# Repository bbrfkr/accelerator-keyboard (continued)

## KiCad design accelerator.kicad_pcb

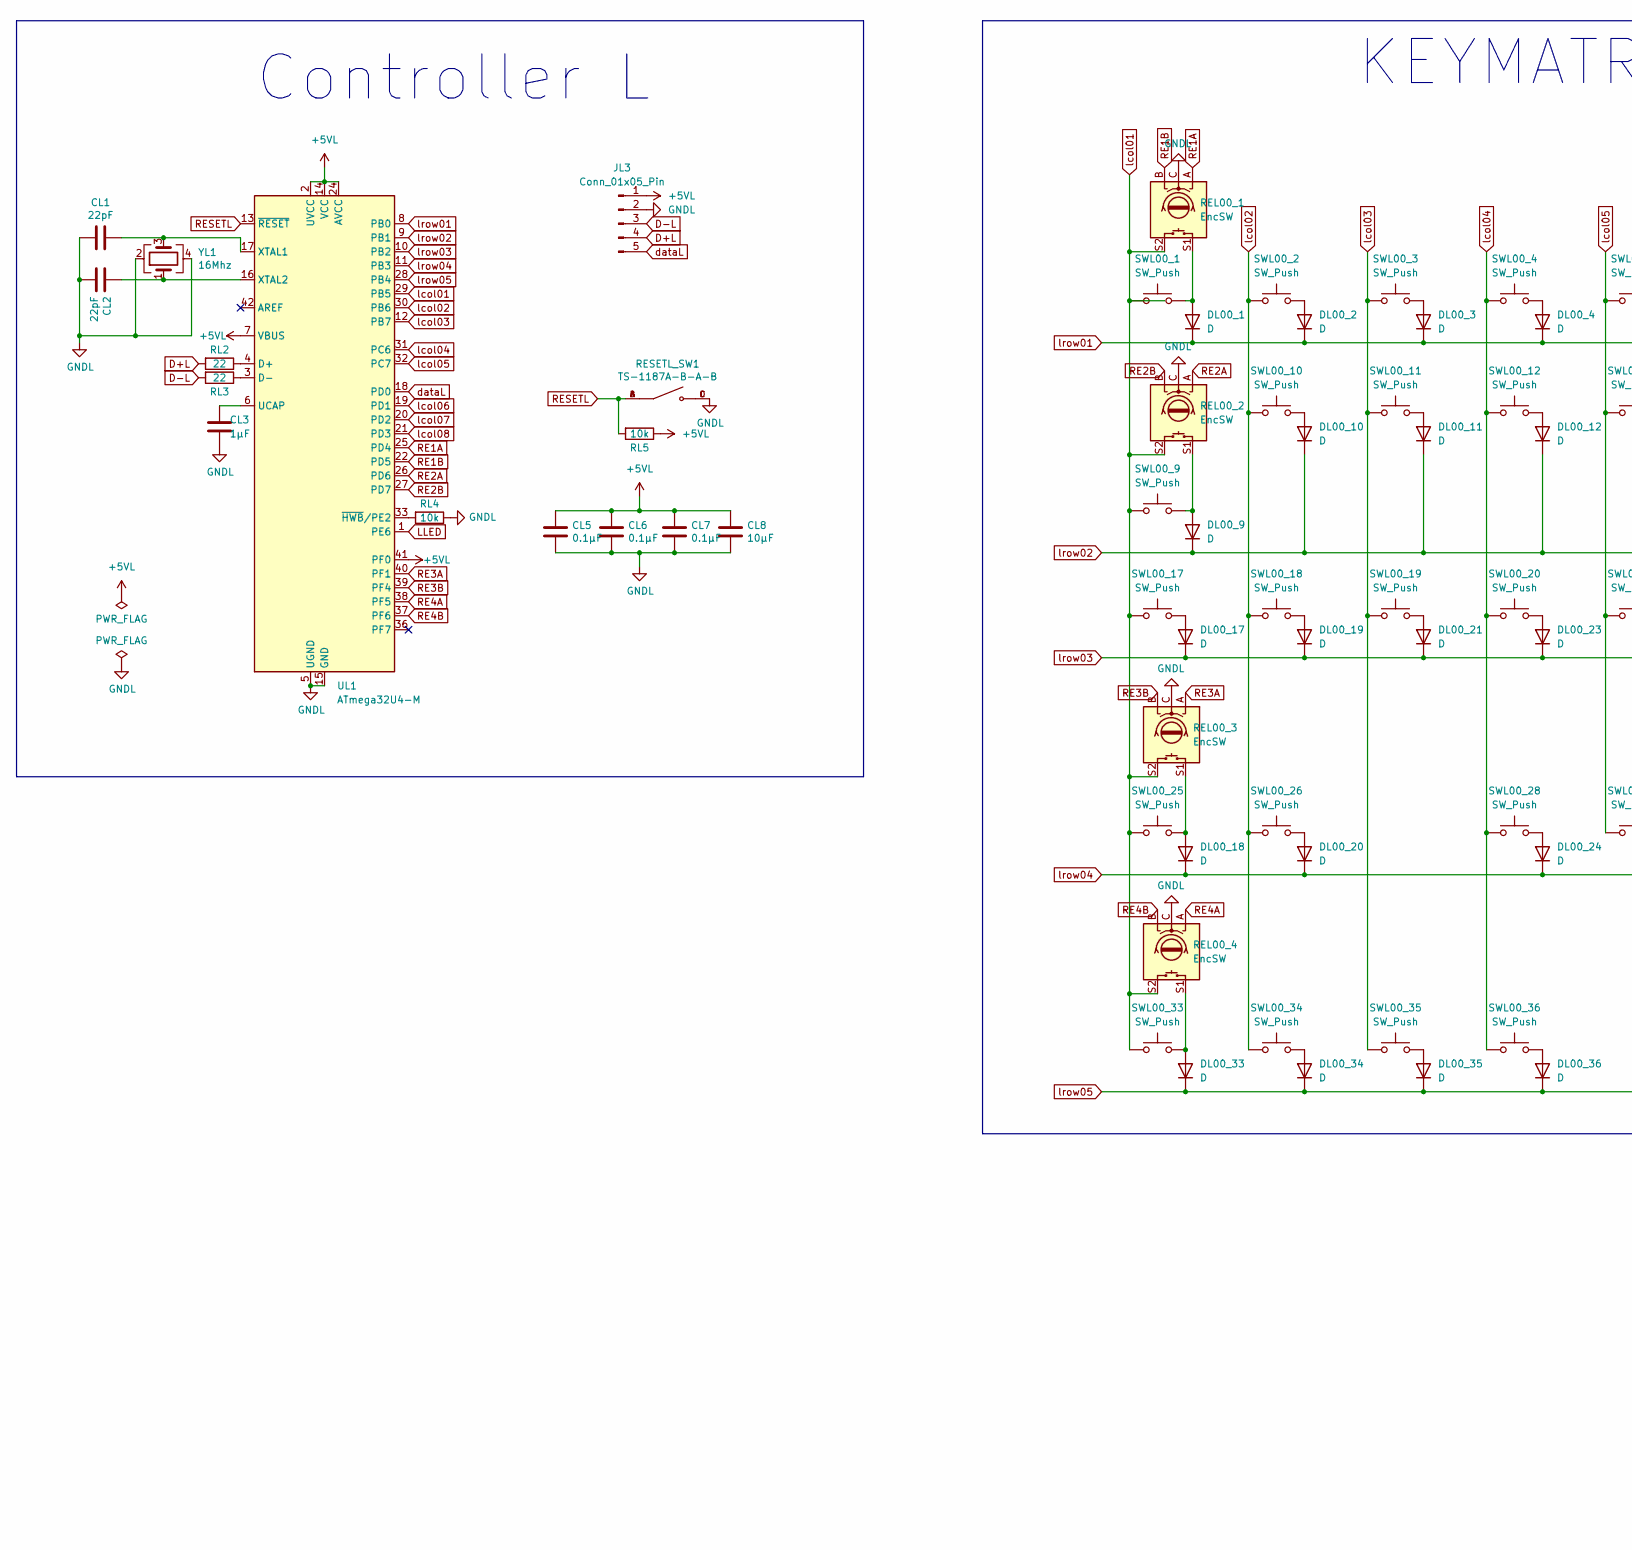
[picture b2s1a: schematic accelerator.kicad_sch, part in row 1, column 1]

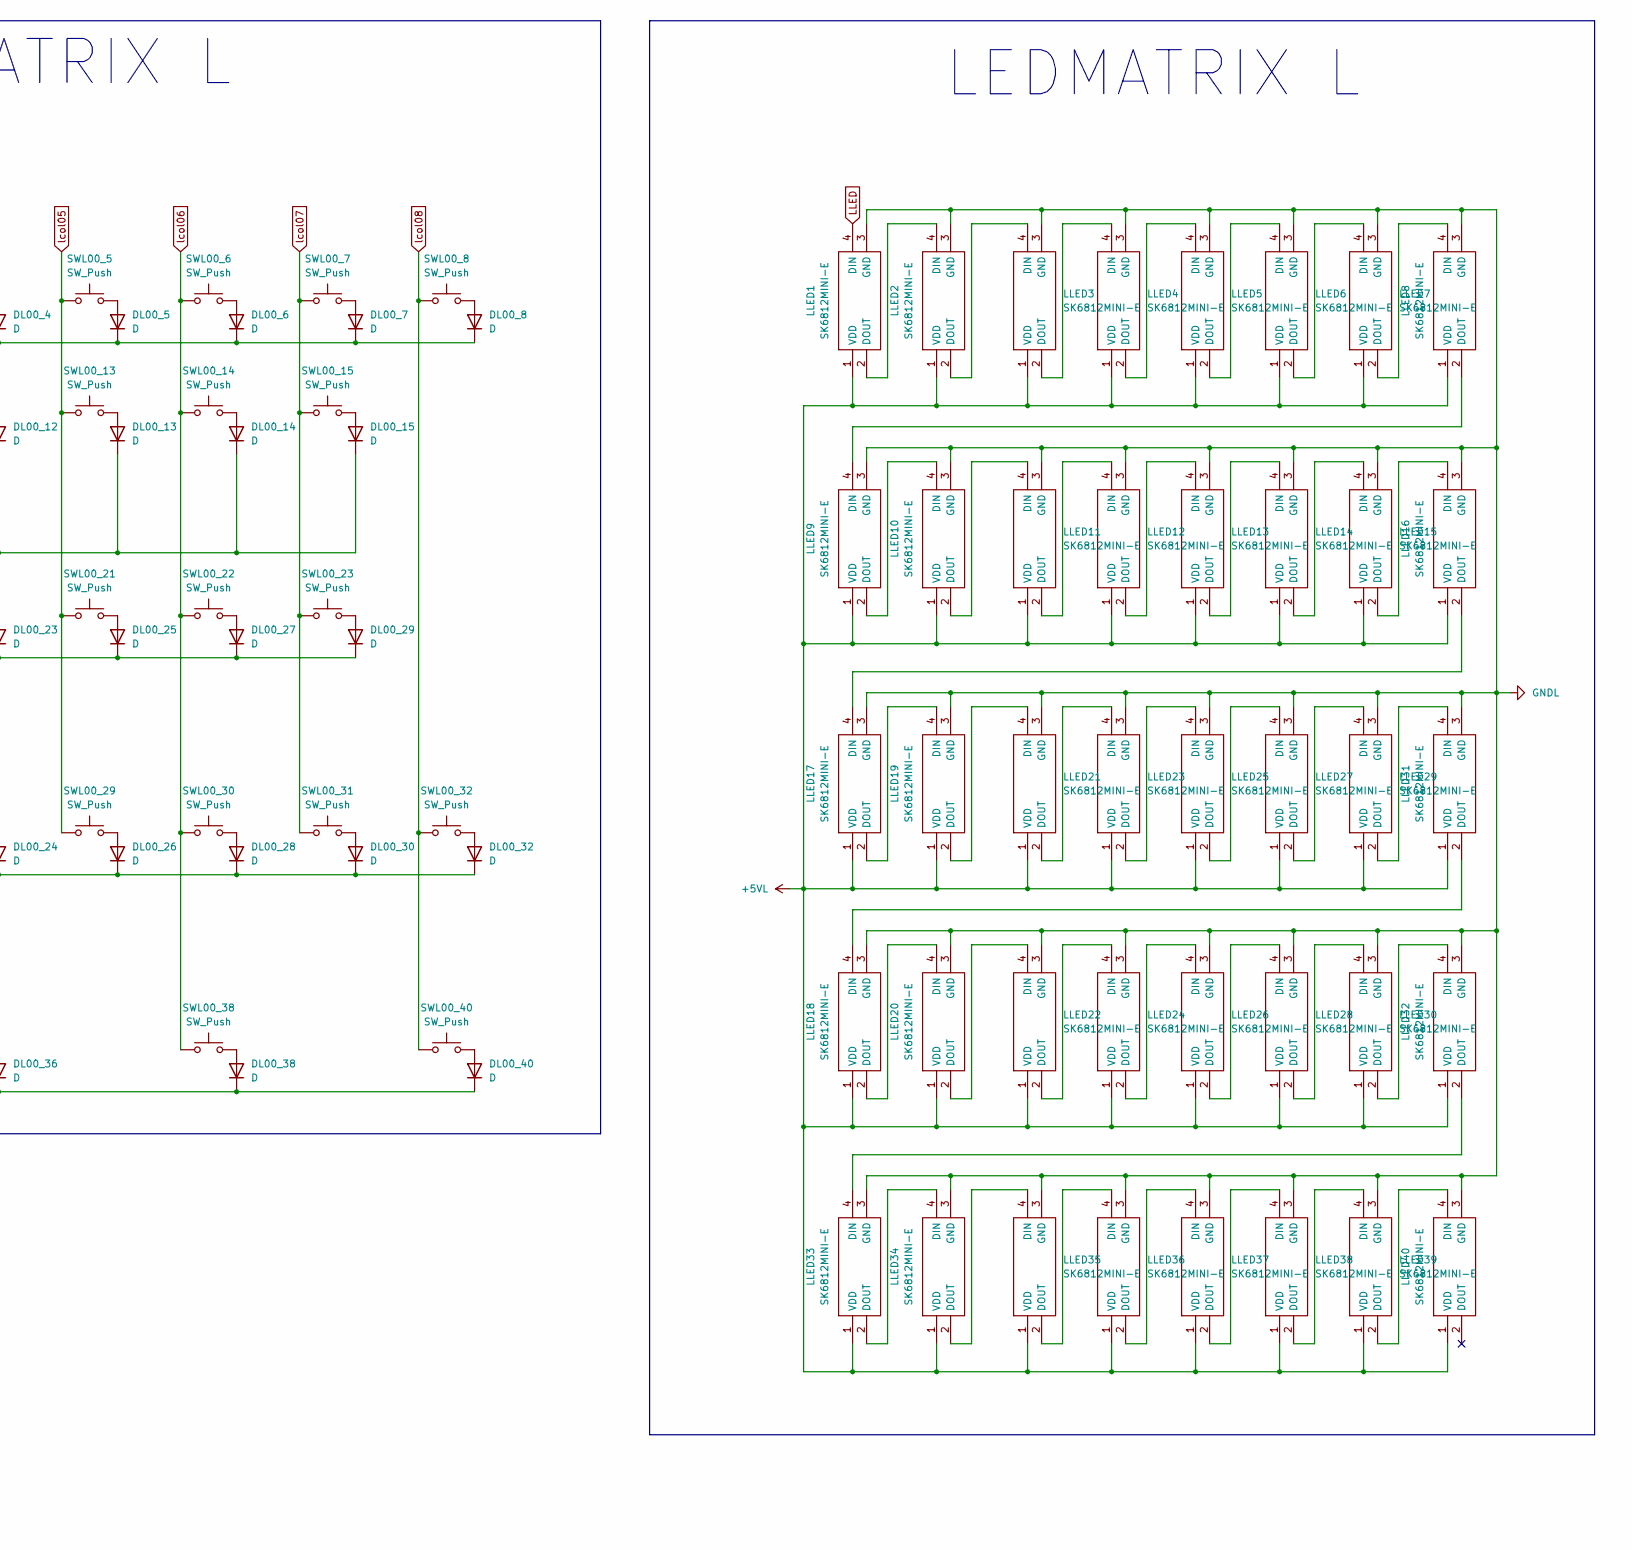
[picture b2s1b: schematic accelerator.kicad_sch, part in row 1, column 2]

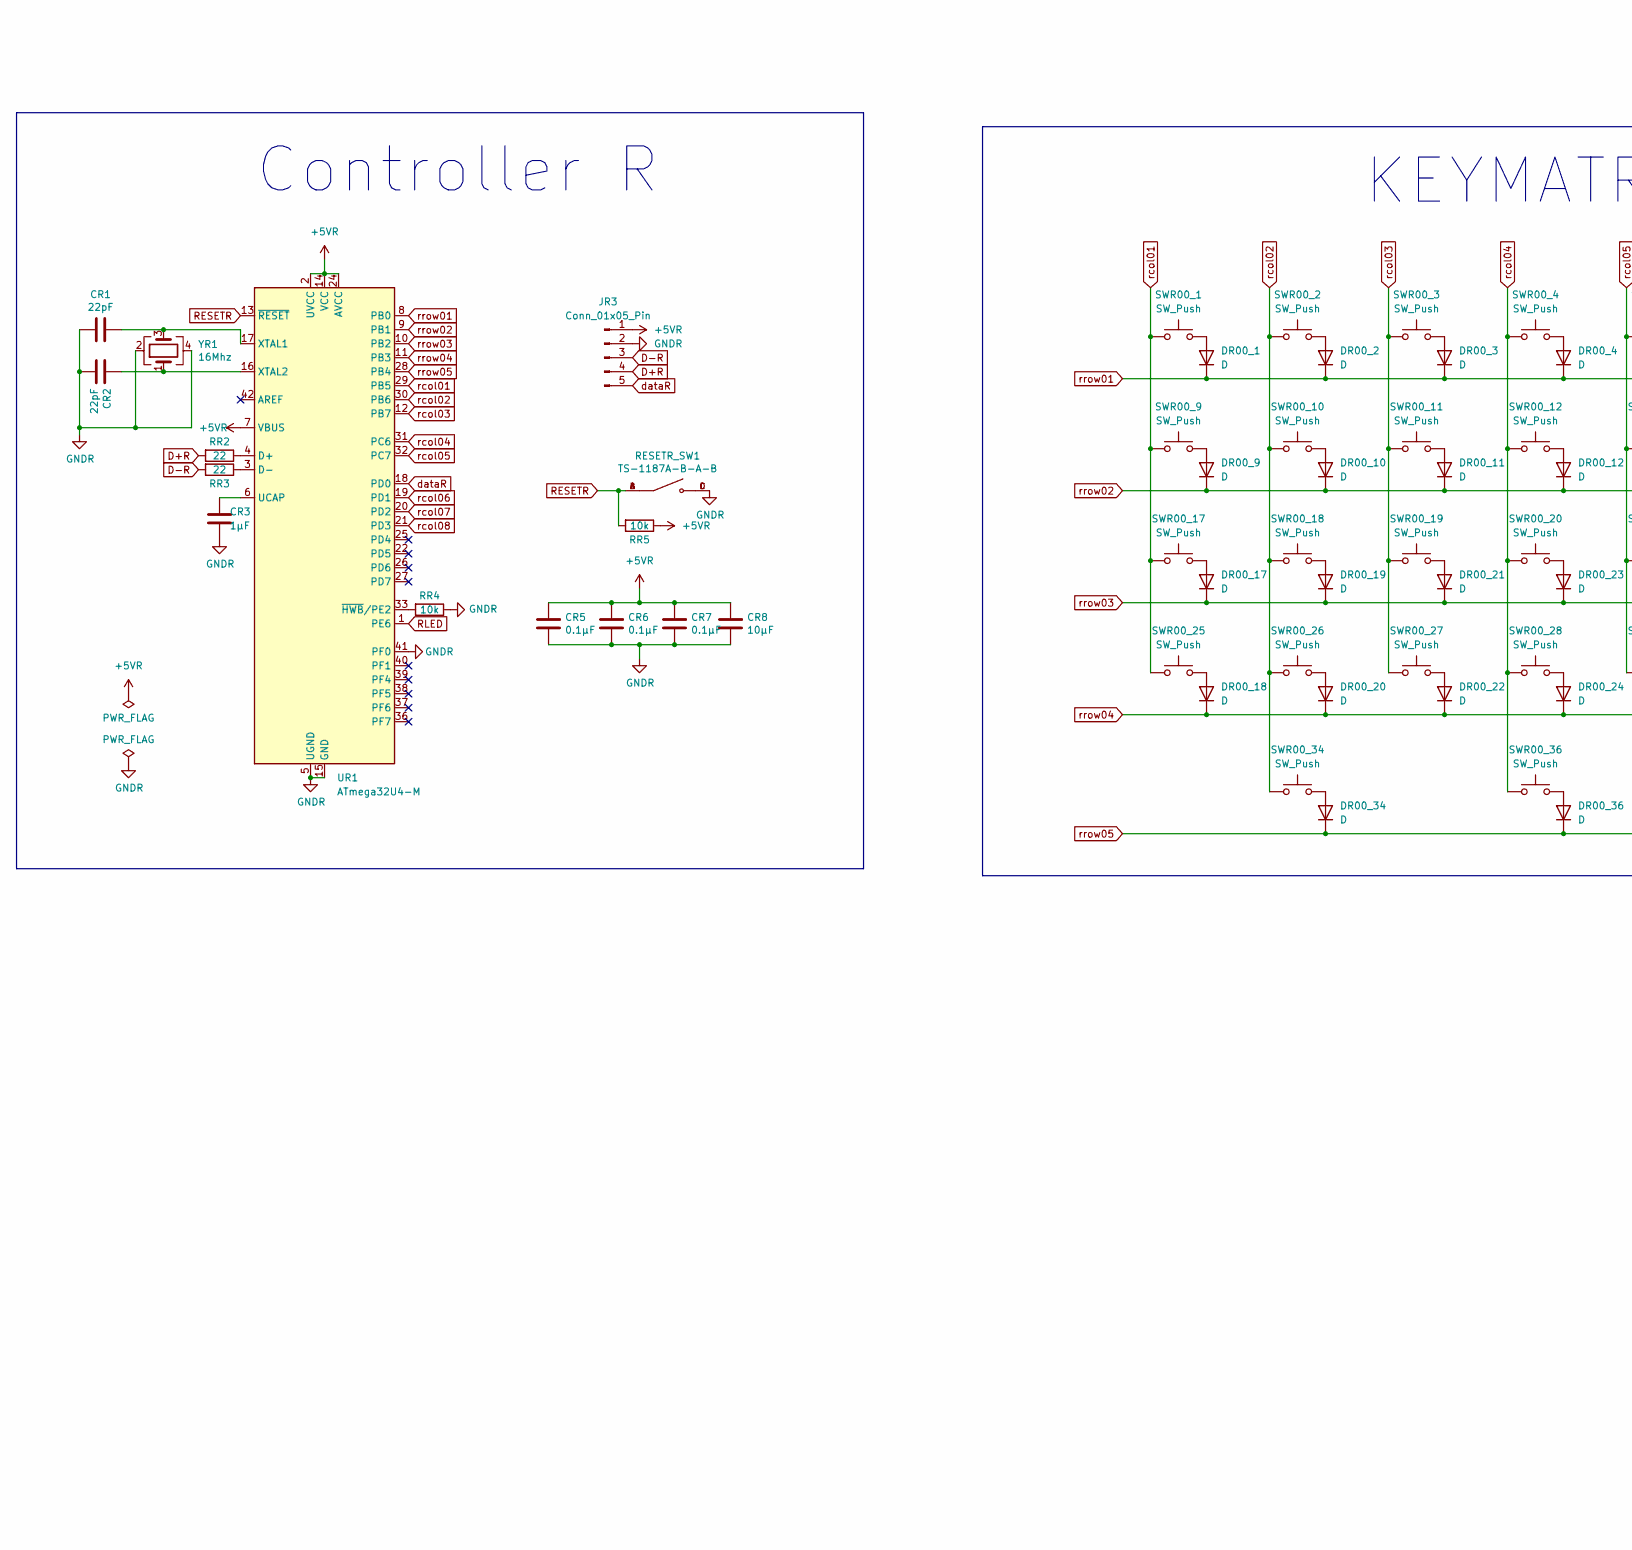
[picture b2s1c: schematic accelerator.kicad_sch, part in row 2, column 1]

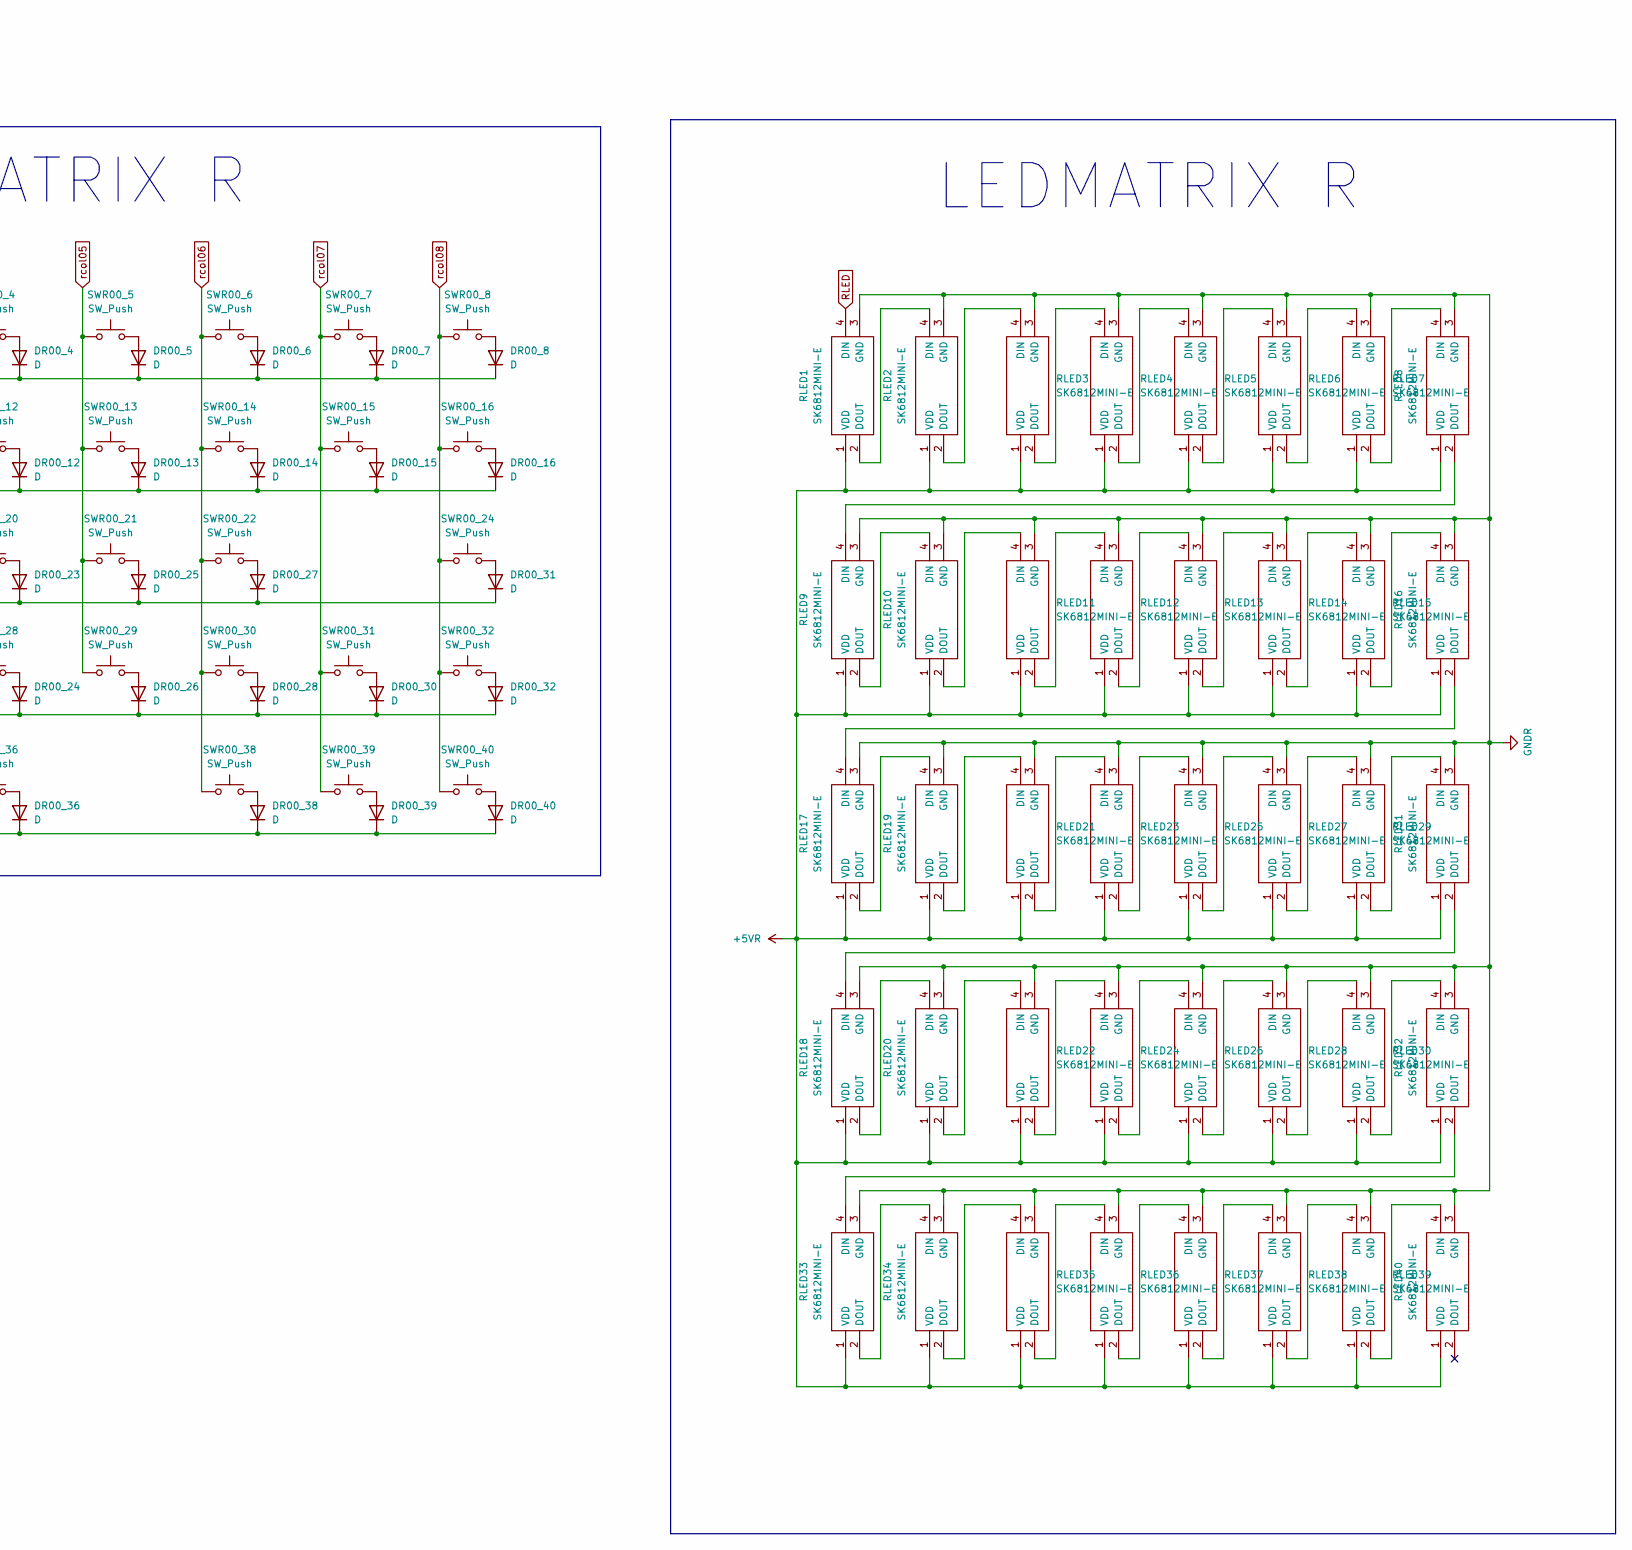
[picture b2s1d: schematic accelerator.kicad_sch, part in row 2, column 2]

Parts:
CL1, CL2: 22pF; C_1206_3216Metric; LCSC C107174
CL3: 1μF; C_1206_3216Metric; LCSC C1848
CL5, CL6, CL7: 0.1μF; C_1206_3216Metric; LCSC C24497
CL8: 10μF; C_1206_3216Metric; LCSC C13585
CR1, CR2: 22pF; C_1206_3216Metric; LCSC C107174
CR3: 1μF; C_1206_3216Metric; LCSC C1848
CR5, CR6, CR7: 0.1μF; C_1206_3216Metric; LCSC C24497
CR8: 10μF; C_1206_3216Metric; LCSC C13585
DL00_1, DL00_2, DL00_3, DL00_4, DL00_5, DL00_6, DL00_7, DL00_8, DL00_9, DL00_10, DL00_11, DL00_12, DL00_13, DL00_14, DL00_15, DL00_17, DL00_18, DL00_19, DL00_20, DL00_21, DL00_23, DL00_24, DL00_25, DL00_26, DL00_27, DL00_28, DL00_29, DL00_30, DL00_32, DL00_33, DL00_34, DL00_35, DL00_36, DL00_38, DL00_40: D; D_SOD-123-Pretty; LCSC C81598
DR00_1, DR00_2, DR00_3, DR00_4, DR00_5, DR00_6, DR00_7, DR00_8, DR00_9, DR00_10, DR00_11, DR00_12, DR00_13, DR00_14, DR00_15, DR00_16, DR00_17, DR00_18, DR00_19, DR00_20, DR00_21, DR00_22, DR00_23, DR00_24, DR00_25, DR00_26, DR00_27, DR00_28, DR00_30, DR00_31, DR00_32, DR00_34, DR00_36, DR00_38, DR00_39, DR00_40: D; D_SOD-123-Pretty; LCSC C81598
JL3: Conn_01x05_Pin; JST_PH_S5B-PH-K_1x05_P2.00mm_Horizontal
JR3: Conn_01x05_Pin; JST_PH_S5B-PH-K_1x05_P2.00mm_Horizontal
LLED1, LLED2, LLED3, LLED4, LLED5, LLED6, LLED7, LLED8, LLED9, LLED10, LLED11, LLED12, LLED13, LLED14, LLED15, LLED16, LLED17, LLED18, LLED19, LLED20, LLED21, LLED22, LLED23, LLED24, LLED25, LLED26, LLED27, LLED28, LLED29, LLED30, LLED31, LLED32, LLED33, LLED34, LLED35, LLED36, LLED37, LLED38, LLED39, LLED40: SK6812MINI-E; SK6812MINIE; Manufacturer_Part_Number SK6812MINI-E; LCSC C5149201
REL00_1, REL00_2, REL00_3, REL00_4: EncSW; RotaryEncoder_Alps_EC12E-Switch_Vertical_H20mm
RESETL_SW1: TS-1187A-B-A-B; SW_TS-1187A-B-A-B; PARTREV A0; LCSC C318884
RESETR_SW1: TS-1187A-B-A-B; SW_TS-1187A-B-A-B; PARTREV A0; LCSC C318884
RL2, RL3: 22; R_1206_3216Metric; LCSC C17958
RL4, RL5: 10k; R_1206_3216Metric; LCSC C17928
RLED1, RLED2, RLED3, RLED4, RLED5, RLED6, RLED7, RLED8, RLED9, RLED10, RLED11, RLED12, RLED13, RLED14, RLED15, RLED16, RLED17, RLED18, RLED19, RLED20, RLED21, RLED22, RLED23, RLED24, RLED25, RLED26, RLED27, RLED28, RLED29, RLED30, RLED31, RLED32, RLED33, RLED34, RLED35, RLED36, RLED37, RLED38, RLED39, RLED40: SK6812MINI-E; SK6812MINIE; Manufacturer_Part_Number SK6812MINI-E; LCSC C5149201
RR2, RR3: 22; R_1206_3216Metric; LCSC C17958
RR4, RR5: 10k; R_1206_3216Metric; LCSC C17928
SWL00_1, SWL00_2, SWL00_3, SWL00_4, SWL00_5, SWL00_6, SWL00_7, SWL00_8, SWL00_9, SWL00_11, SWL00_12, SWL00_13, SWL00_14, SWL00_15, SWL00_17, SWL00_19, SWL00_20, SWL00_21, SWL00_22, SWL00_23, SWL00_25, SWL00_28, SWL00_29, SWL00_30, SWL00_31, SWL00_32, SWL00_33: SW_Push; MXOnly-1U-Hotswap; LCSC C5156480
SWL00_10: SW_Push; MXOnly-1.5U-Hotswap; LCSC C5156480
SWL00_18: SW_Push; MXOnly-1.75U-Hotswap; LCSC C5156480
SWL00_26: SW_Push; MXOnly-2.25U-Hotswap; LCSC C5156480
SWL00_34, SWL00_35, SWL00_36, SWL00_40: SW_Push; MXOnly-1.25U-Hotswap; LCSC C5156480
SWL00_38: SW_Push; MXOnly-2.25U-Hotswap-ReversedStabilizers; LCSC C5156480
SWR00_1, SWR00_2, SWR00_3, SWR00_4, SWR00_5, SWR00_6, SWR00_7, SWR00_9, SWR00_10, SWR00_11, SWR00_12, SWR00_13, SWR00_14, SWR00_15, SWR00_17, SWR00_18, SWR00_19, SWR00_20, SWR00_21, SWR00_22, SWR00_25, SWR00_26, SWR00_27, SWR00_28, SWR00_29, SWR00_30, SWR00_32: SW_Push; MXOnly-1U-Hotswap; LCSC C5156480
SWR00_8: SW_Push; MXOnly-2U-Hotswap; LCSC C5156480
SWR00_16: SW_Push; MXOnly-1.5U-Hotswap; LCSC C5156480
SWR00_24: SW_Push; MXOnly-2.25U-Hotswap; LCSC C5156480
SWR00_31: SW_Push; MXOnly-1.75U-Hotswap; LCSC C5156480
SWR00_34: SW_Push; MXOnly-2.75U-Hotswap-ReversedStabilizers; LCSC C5156480
SWR00_36: SW_Push; MXOnly-2.25U-Hotswap-ReversedStabilizers; LCSC C5156480
SWR00_38, SWR00_39, SWR00_40: SW_Push; MXOnly-1.25U-Hotswap; LCSC C5156480
UL1: ATmega32U4-M; QFN-44-1EP_7x7mm_P0.5mm_EP5.2x5.2mm; LCSC C112161
UR1: ATmega32U4-M; QFN-44-1EP_7x7mm_P0.5mm_EP5.2x5.2mm; LCSC C112161
YL1: 16Mhz; OSC-SMD_4P-L3.2-W2.5-BL; LCSC C13738
YR1: 16Mhz; OSC-SMD_4P-L3.2-W2.5-BL; LCSC C13738

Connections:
+5VL: CL5.1, CL6.1, CL7.1, CL8.1, JL3.1, LLED1.1 (VDD), LLED2.1 (VDD), LLED3.1 (VDD), LLED4.1 (VDD), LLED5.1 (VDD), LLED6.1 (VDD), LLED7.1 (VDD), LLED8.1 (VDD), LLED9.1 (VDD), LLED10.1 (VDD), LLED11.1 (VDD), LLED12.1 (VDD), LLED13.1 (VDD), LLED14.1 (VDD), LLED15.1 (VDD), LLED16.1 (VDD), LLED17.1 (VDD), LLED18.1 (VDD), LLED19.1 (VDD), LLED20.1 (VDD), LLED21.1 (VDD), LLED22.1 (VDD), LLED23.1 (VDD), LLED24.1 (VDD), LLED25.1 (VDD), LLED26.1 (VDD), LLED27.1 (VDD), LLED28.1 (VDD), LLED29.1 (VDD), LLED30.1 (VDD), LLED31.1 (VDD), LLED32.1 (VDD), LLED33.1 (VDD), LLED34.1 (VDD), LLED35.1 (VDD), LLED36.1 (VDD), LLED37.1 (VDD), LLED38.1 (VDD), LLED39.1 (VDD), LLED40.1 (VDD), RL5.1, UL1.2 (UVCC), UL1.7 (VBUS), UL1.14 (VCC), UL1.24 (AVCC), UL1.34 (VCC), UL1.41 (PF0), UL1.44 (AVCC)
+5VR: CR5.1, CR6.1, CR7.1, CR8.1, JR3.1, RLED1.1 (VDD), RLED2.1 (VDD), RLED3.1 (VDD), RLED4.1 (VDD), RLED5.1 (VDD), RLED6.1 (VDD), RLED7.1 (VDD), RLED8.1 (VDD), RLED9.1 (VDD), RLED10.1 (VDD), RLED11.1 (VDD), RLED12.1 (VDD), RLED13.1 (VDD), RLED14.1 (VDD), RLED15.1 (VDD), RLED16.1 (VDD), RLED17.1 (VDD), RLED18.1 (VDD), RLED19.1 (VDD), RLED20.1 (VDD), RLED21.1 (VDD), RLED22.1 (VDD), RLED23.1 (VDD), RLED24.1 (VDD), RLED25.1 (VDD), RLED26.1 (VDD), RLED27.1 (VDD), RLED28.1 (VDD), RLED29.1 (VDD), RLED30.1 (VDD), RLED31.1 (VDD), RLED32.1 (VDD), RLED33.1 (VDD), RLED34.1 (VDD), RLED35.1 (VDD), RLED36.1 (VDD), RLED37.1 (VDD), RLED38.1 (VDD), RLED39.1 (VDD), RLED40.1 (VDD), RR5.1, UR1.2 (UVCC), UR1.7 (VBUS), UR1.14 (VCC), UR1.24 (AVCC), UR1.34 (VCC), UR1.44 (AVCC)
D+L: JL3.4, RL2.2
D+R: JR3.4, RR2.2
D-L: JL3.3, RL3.2
D-R: JR3.3, RR3.2
GNDL: CL1.1, CL2.2, CL3.2, CL5.2, CL6.2, CL7.2, CL8.2, JL3.2, LLED1.3 (GND), LLED2.3 (GND), LLED3.3 (GND), LLED4.3 (GND), LLED5.3 (GND), LLED6.3 (GND), LLED7.3 (GND), LLED8.3 (GND), LLED9.3 (GND), LLED10.3 (GND), LLED11.3 (GND), LLED12.3 (GND), LLED13.3 (GND), LLED14.3 (GND), LLED15.3 (GND), LLED16.3 (GND), LLED17.3 (GND), LLED18.3 (GND), LLED19.3 (GND), LLED20.3 (GND), LLED21.3 (GND), LLED22.3 (GND), LLED23.3 (GND), LLED24.3 (GND), LLED25.3 (GND), LLED26.3 (GND), LLED27.3 (GND), LLED28.3 (GND), LLED29.3 (GND), LLED30.3 (GND), LLED31.3 (GND), LLED32.3 (GND), LLED33.3 (GND), LLED34.3 (GND), LLED35.3 (GND), LLED36.3 (GND), LLED37.3 (GND), LLED38.3 (GND), LLED39.3 (GND), LLED40.3 (GND), REL00_1.C, REL00_2.C, REL00_3.C, REL00_4.C, RESETL_SW1.C, RESETL_SW1.D, RL4.1, UL1.5 (UGND), UL1.15 (GND), UL1.23 (GND), UL1.35 (GND), UL1.43 (GND), UL1.45 (GND), YL1.2, YL1.4
GNDR: CR1.1, CR2.2, CR3.2, CR5.2, CR6.2, CR7.2, CR8.2, JR3.2, RESETR_SW1.C, RESETR_SW1.D, RLED1.3 (GND), RLED2.3 (GND), RLED3.3 (GND), RLED4.3 (GND), RLED5.3 (GND), RLED6.3 (GND), RLED7.3 (GND), RLED8.3 (GND), RLED9.3 (GND), RLED10.3 (GND), RLED11.3 (GND), RLED12.3 (GND), RLED13.3 (GND), RLED14.3 (GND), RLED15.3 (GND), RLED16.3 (GND), RLED17.3 (GND), RLED18.3 (GND), RLED19.3 (GND), RLED20.3 (GND), RLED21.3 (GND), RLED22.3 (GND), RLED23.3 (GND), RLED24.3 (GND), RLED25.3 (GND), RLED26.3 (GND), RLED27.3 (GND), RLED28.3 (GND), RLED29.3 (GND), RLED30.3 (GND), RLED31.3 (GND), RLED32.3 (GND), RLED33.3 (GND), RLED34.3 (GND), RLED35.3 (GND), RLED36.3 (GND), RLED37.3 (GND), RLED38.3 (GND), RLED39.3 (GND), RLED40.3 (GND), RR4.1, UR1.5 (UGND), UR1.15 (GND), UR1.23 (GND), UR1.35 (GND), UR1.41 (PF0), UR1.43 (GND), UR1.45 (GND), YR1.2, YR1.4
LLED: LLED1.4 (DIN), UL1.1 (PE6)
unnamed: DL00_1.2 (A), REL00_1.S1, SWL00_1.2
unnamed: DL00_2.2 (A), SWL00_2.2
unnamed: DL00_3.2 (A), SWL00_3.2
unnamed: DL00_4.2 (A), SWL00_4.2
unnamed: DL00_5.2 (A), SWL00_5.2
unnamed: DL00_6.2 (A), SWL00_6.2
unnamed: DL00_7.2 (A), SWL00_7.2
unnamed: DL00_8.2 (A), SWL00_8.2
unnamed: DL00_9.2 (A), REL00_2.S1, SWL00_9.2
unnamed: DL00_10.2 (A), SWL00_10.2
unnamed: DL00_11.2 (A), SWL00_11.2
unnamed: DL00_12.2 (A), SWL00_12.2
unnamed: DL00_13.2 (A), SWL00_13.2
unnamed: DL00_14.2 (A), SWL00_14.2
unnamed: DL00_15.2 (A), SWL00_15.2
unnamed: DL00_17.2 (A), SWL00_17.2
unnamed: DL00_18.2 (A), REL00_3.S1, SWL00_25.2
unnamed: DL00_19.2 (A), SWL00_18.2
unnamed: DL00_20.2 (A), SWL00_26.2
unnamed: DL00_21.2 (A), SWL00_19.2
unnamed: DL00_23.2 (A), SWL00_20.2
unnamed: DL00_24.2 (A), SWL00_28.2
unnamed: DL00_25.2 (A), SWL00_21.2
unnamed: DL00_26.2 (A), SWL00_29.2
unnamed: DL00_27.2 (A), SWL00_22.2
unnamed: DL00_28.2 (A), SWL00_30.2
unnamed: DL00_29.2 (A), SWL00_23.2
unnamed: DL00_30.2 (A), SWL00_31.2
unnamed: DL00_32.2 (A), SWL00_32.2
unnamed: DL00_33.2 (A), REL00_4.S1, SWL00_33.2
unnamed: DL00_34.2 (A), SWL00_34.2
unnamed: DL00_35.2 (A), SWL00_35.2
unnamed: DL00_36.2 (A), SWL00_36.2
unnamed: DL00_38.2 (A), SWL00_38.2
unnamed: DL00_40.2 (A), SWL00_40.2
unnamed: DR00_1.2 (A), SWR00_1.2
unnamed: DR00_2.2 (A), SWR00_2.2
unnamed: DR00_3.2 (A), SWR00_3.2
unnamed: DR00_4.2 (A), SWR00_4.2
unnamed: DR00_5.2 (A), SWR00_5.2
unnamed: DR00_6.2 (A), SWR00_6.2
unnamed: DR00_7.2 (A), SWR00_7.2
unnamed: DR00_8.2 (A), SWR00_8.2
unnamed: DR00_9.2 (A), SWR00_9.2
unnamed: DR00_10.2 (A), SWR00_10.2
unnamed: DR00_11.2 (A), SWR00_11.2
unnamed: DR00_12.2 (A), SWR00_12.2
unnamed: DR00_13.2 (A), SWR00_13.2
unnamed: DR00_14.2 (A), SWR00_14.2
unnamed: DR00_15.2 (A), SWR00_15.2
unnamed: DR00_16.2 (A), SWR00_16.2
unnamed: DR00_17.2 (A), SWR00_17.2
unnamed: DR00_18.2 (A), SWR00_25.2
unnamed: DR00_19.2 (A), SWR00_18.2
unnamed: DR00_20.2 (A), SWR00_26.2
unnamed: DR00_21.2 (A), SWR00_19.2
unnamed: DR00_22.2 (A), SWR00_27.2
unnamed: DR00_23.2 (A), SWR00_20.2
unnamed: DR00_24.2 (A), SWR00_28.2
unnamed: DR00_25.2 (A), SWR00_21.2
unnamed: DR00_26.2 (A), SWR00_29.2
unnamed: DR00_27.2 (A), SWR00_22.2
unnamed: DR00_28.2 (A), SWR00_30.2
unnamed: DR00_30.2 (A), SWR00_31.2
unnamed: DR00_31.2 (A), SWR00_24.2
unnamed: DR00_32.2 (A), SWR00_32.2
unnamed: DR00_34.2 (A), SWR00_34.2
unnamed: DR00_36.2 (A), SWR00_36.2
unnamed: DR00_38.2 (A), SWR00_38.2
unnamed: DR00_39.2 (A), SWR00_39.2
unnamed: DR00_40.2 (A), SWR00_40.2
unnamed: LLED1.2 (DOUT), LLED2.4 (DIN)
unnamed: LLED2.2 (DOUT), LLED3.4 (DIN)
unnamed: LLED3.2 (DOUT), LLED4.4 (DIN)
unnamed: LLED4.2 (DOUT), LLED5.4 (DIN)
unnamed: LLED5.2 (DOUT), LLED6.4 (DIN)
unnamed: LLED6.2 (DOUT), LLED7.4 (DIN)
unnamed: LLED7.2 (DOUT), LLED8.4 (DIN)
unnamed: LLED8.2 (DOUT), LLED9.4 (DIN)
unnamed: LLED9.2 (DOUT), LLED10.4 (DIN)
unnamed: LLED10.2 (DOUT), LLED11.4 (DIN)
unnamed: LLED11.2 (DOUT), LLED12.4 (DIN)
unnamed: LLED12.2 (DOUT), LLED13.4 (DIN)
unnamed: LLED13.2 (DOUT), LLED14.4 (DIN)
unnamed: LLED14.2 (DOUT), LLED15.4 (DIN)
unnamed: LLED15.2 (DOUT), LLED16.4 (DIN)
unnamed: LLED16.2 (DOUT), LLED17.4 (DIN)
unnamed: LLED17.2 (DOUT), LLED19.4 (DIN)
unnamed: LLED18.4 (DIN), LLED31.2 (DOUT)
unnamed: LLED18.2 (DOUT), LLED20.4 (DIN)
unnamed: LLED19.2 (DOUT), LLED21.4 (DIN)
unnamed: LLED20.2 (DOUT), LLED22.4 (DIN)
unnamed: LLED21.2 (DOUT), LLED23.4 (DIN)
unnamed: LLED22.2 (DOUT), LLED24.4 (DIN)
unnamed: LLED23.2 (DOUT), LLED25.4 (DIN)
unnamed: LLED24.2 (DOUT), LLED26.4 (DIN)
unnamed: LLED25.2 (DOUT), LLED27.4 (DIN)
unnamed: LLED26.2 (DOUT), LLED28.4 (DIN)
unnamed: LLED27.2 (DOUT), LLED29.4 (DIN)
unnamed: LLED28.2 (DOUT), LLED30.4 (DIN)
unnamed: LLED29.2 (DOUT), LLED31.4 (DIN)
unnamed: LLED30.2 (DOUT), LLED32.4 (DIN)
unnamed: LLED32.2 (DOUT), LLED33.4 (DIN)
unnamed: LLED33.2 (DOUT), LLED34.4 (DIN)
unnamed: LLED34.2 (DOUT), LLED35.4 (DIN)
unnamed: LLED35.2 (DOUT), LLED36.4 (DIN)
unnamed: LLED36.2 (DOUT), LLED37.4 (DIN)
unnamed: LLED37.2 (DOUT), LLED38.4 (DIN)
unnamed: LLED38.2 (DOUT), LLED39.4 (DIN)
unnamed: LLED39.2 (DOUT), LLED40.4 (DIN)
unnamed: RLED1.2 (DOUT), RLED2.4 (DIN)
unnamed: RLED2.2 (DOUT), RLED3.4 (DIN)
unnamed: RLED3.2 (DOUT), RLED4.4 (DIN)
unnamed: RLED4.2 (DOUT), RLED5.4 (DIN)
unnamed: RLED5.2 (DOUT), RLED6.4 (DIN)
unnamed: RLED6.2 (DOUT), RLED7.4 (DIN)
unnamed: RLED7.2 (DOUT), RLED8.4 (DIN)
unnamed: RLED8.2 (DOUT), RLED9.4 (DIN)
unnamed: RLED9.2 (DOUT), RLED10.4 (DIN)
unnamed: RLED10.2 (DOUT), RLED11.4 (DIN)
unnamed: RLED11.2 (DOUT), RLED12.4 (DIN)
unnamed: RLED12.2 (DOUT), RLED13.4 (DIN)
unnamed: RLED13.2 (DOUT), RLED14.4 (DIN)
unnamed: RLED14.2 (DOUT), RLED15.4 (DIN)
unnamed: RLED15.2 (DOUT), RLED16.4 (DIN)
unnamed: RLED16.2 (DOUT), RLED17.4 (DIN)
unnamed: RLED17.2 (DOUT), RLED19.4 (DIN)
unnamed: RLED18.4 (DIN), RLED31.2 (DOUT)
unnamed: RLED18.2 (DOUT), RLED20.4 (DIN)
unnamed: RLED19.2 (DOUT), RLED21.4 (DIN)
unnamed: RLED20.2 (DOUT), RLED22.4 (DIN)
unnamed: RLED21.2 (DOUT), RLED23.4 (DIN)
unnamed: RLED22.2 (DOUT), RLED24.4 (DIN)
unnamed: RLED23.2 (DOUT), RLED25.4 (DIN)
unnamed: RLED24.2 (DOUT), RLED26.4 (DIN)
unnamed: RLED25.2 (DOUT), RLED27.4 (DIN)
unnamed: RLED26.2 (DOUT), RLED28.4 (DIN)
unnamed: RLED27.2 (DOUT), RLED29.4 (DIN)
unnamed: RLED28.2 (DOUT), RLED30.4 (DIN)
unnamed: RLED29.2 (DOUT), RLED31.4 (DIN)
unnamed: RLED30.2 (DOUT), RLED32.4 (DIN)
unnamed: RLED32.2 (DOUT), RLED33.4 (DIN)
unnamed: RLED33.2 (DOUT), RLED34.4 (DIN)
unnamed: RLED34.2 (DOUT), RLED35.4 (DIN)
unnamed: RLED35.2 (DOUT), RLED36.4 (DIN)
unnamed: RLED36.2 (DOUT), RLED37.4 (DIN)
unnamed: RLED37.2 (DOUT), RLED38.4 (DIN)
unnamed: RLED38.2 (DOUT), RLED39.4 (DIN)
unnamed: RLED39.2 (DOUT), RLED40.4 (DIN)
unnamed: RL2.1, UL1.4 (D+)
unnamed: RL3.1, UL1.3 (D-)
unnamed: CL3.1, UL1.6 (UCAP)
unnamed: CL1.2, UL1.17 (XTAL1), YL1.3
unnamed: CL2.1, UL1.16 (XTAL2), YL1.1
unnamed: RL4.2, UL1.33 (~HWB/PE2)
unnamed: RR2.1, UR1.4 (D+)
unnamed: RR3.1, UR1.3 (D-)
unnamed: CR3.1, UR1.6 (UCAP)
unnamed: CR1.2, UR1.17 (XTAL1), YR1.3
unnamed: CR2.1, UR1.16 (XTAL2), YR1.1
unnamed: RR4.2, UR1.33 (~HWB/PE2)
RE1A: REL00_1.A, UL1.25 (PD4)
RE1B: REL00_1.B, UL1.22 (PD5)
RE2A: REL00_2.A, UL1.26 (PD6)
RE2B: REL00_2.B, UL1.27 (PD7)
RE3A: REL00_3.A, UL1.40 (PF1)
RE3B: REL00_3.B, UL1.39 (PF4)
RE4A: REL00_4.A, UL1.38 (PF5)
RE4B: REL00_4.B, UL1.37 (PF6)
RESETL: RESETL_SW1.A, RESETL_SW1.B, RL5.2, UL1.13 (~RESET)
RESETR: RESETR_SW1.A, RESETR_SW1.B, RR5.2, UR1.13 (~RESET)
RLED: RLED1.4 (DIN), UR1.1 (PE6)
dataL: JL3.5, UL1.18 (PD0)
dataR: JR3.5, UR1.18 (PD0)
lcol01: REL00_1.S2, REL00_2.S2, REL00_3.S2, REL00_4.S2, SWL00_1.1, SWL00_9.1, SWL00_17.1, SWL00_25.1, SWL00_33.1, UL1.29 (PB5)
lcol02: SWL00_2.1, SWL00_10.1, SWL00_18.1, SWL00_26.1, SWL00_34.1, UL1.30 (PB6)
lcol03: SWL00_3.1, SWL00_11.1, SWL00_19.1, SWL00_35.1, UL1.12 (PB7)
lcol04: SWL00_4.1, SWL00_12.1, SWL00_20.1, SWL00_28.1, SWL00_36.1, UL1.31 (PC6)
lcol05: SWL00_5.1, SWL00_13.1, SWL00_21.1, SWL00_29.1, UL1.32 (PC7)
lcol06: SWL00_6.1, SWL00_14.1, SWL00_22.1, SWL00_30.1, SWL00_38.1, UL1.19 (PD1)
lcol07: SWL00_7.1, SWL00_15.1, SWL00_23.1, SWL00_31.1, UL1.20 (PD2)
lcol08: SWL00_8.1, SWL00_32.1, SWL00_40.1, UL1.21 (PD3)
lrow01: DL00_1.1 (K), DL00_2.1 (K), DL00_3.1 (K), DL00_4.1 (K), DL00_5.1 (K), DL00_6.1 (K), DL00_7.1 (K), DL00_8.1 (K), UL1.8 (PB0)
lrow02: DL00_9.1 (K), DL00_10.1 (K), DL00_11.1 (K), DL00_12.1 (K), DL00_13.1 (K), DL00_14.1 (K), DL00_15.1 (K), UL1.9 (PB1)
lrow03: DL00_17.1 (K), DL00_19.1 (K), DL00_21.1 (K), DL00_23.1 (K), DL00_25.1 (K), DL00_27.1 (K), DL00_29.1 (K), UL1.10 (PB2)
lrow04: DL00_18.1 (K), DL00_20.1 (K), DL00_24.1 (K), DL00_26.1 (K), DL00_28.1 (K), DL00_30.1 (K), DL00_32.1 (K), UL1.11 (PB3)
lrow05: DL00_33.1 (K), DL00_34.1 (K), DL00_35.1 (K), DL00_36.1 (K), DL00_38.1 (K), DL00_40.1 (K), UL1.28 (PB4)
rcol01: SWR00_1.1, SWR00_9.1, SWR00_17.1, SWR00_25.1, UR1.29 (PB5)
rcol02: SWR00_2.1, SWR00_10.1, SWR00_18.1, SWR00_26.1, SWR00_34.1, UR1.30 (PB6)
rcol03: SWR00_3.1, SWR00_11.1, SWR00_19.1, SWR00_27.1, UR1.12 (PB7)
rcol04: SWR00_4.1, SWR00_12.1, SWR00_20.1, SWR00_28.1, SWR00_36.1, UR1.31 (PC6)
rcol05: SWR00_5.1, SWR00_13.1, SWR00_21.1, SWR00_29.1, UR1.32 (PC7)
rcol06: SWR00_6.1, SWR00_14.1, SWR00_22.1, SWR00_30.1, SWR00_38.1, UR1.19 (PD1)
rcol07: SWR00_7.1, SWR00_15.1, SWR00_31.1, SWR00_39.1, UR1.20 (PD2)
rcol08: SWR00_8.1, SWR00_16.1, SWR00_24.1, SWR00_32.1, SWR00_40.1, UR1.21 (PD3)
rrow01: DR00_1.1 (K), DR00_2.1 (K), DR00_3.1 (K), DR00_4.1 (K), DR00_5.1 (K), DR00_6.1 (K), DR00_7.1 (K), DR00_8.1 (K), UR1.8 (PB0)
rrow02: DR00_9.1 (K), DR00_10.1 (K), DR00_11.1 (K), DR00_12.1 (K), DR00_13.1 (K), DR00_14.1 (K), DR00_15.1 (K), DR00_16.1 (K), UR1.9 (PB1)
rrow03: DR00_17.1 (K), DR00_19.1 (K), DR00_21.1 (K), DR00_23.1 (K), DR00_25.1 (K), DR00_27.1 (K), DR00_31.1 (K), UR1.10 (PB2)
rrow04: DR00_18.1 (K), DR00_20.1 (K), DR00_22.1 (K), DR00_24.1 (K), DR00_26.1 (K), DR00_28.1 (K), DR00_30.1 (K), DR00_32.1 (K), UR1.11 (PB3)
rrow05: DR00_34.1 (K), DR00_36.1 (K), DR00_38.1 (K), DR00_39.1 (K), DR00_40.1 (K), UR1.28 (PB4)

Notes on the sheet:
Controller R
KEYMATRIX R
LEDMATRIX L
LEDMATRIX R
KEYMATRIX L
Controller L

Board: 2 copper layers, 256 parts (0 on the bottom side), 209 nets, no tracks yet.

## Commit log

2024-05-06 impl daughterboard and plate
2024-06-08 ordered
2024-07-12 impl daughterboard and firmware
